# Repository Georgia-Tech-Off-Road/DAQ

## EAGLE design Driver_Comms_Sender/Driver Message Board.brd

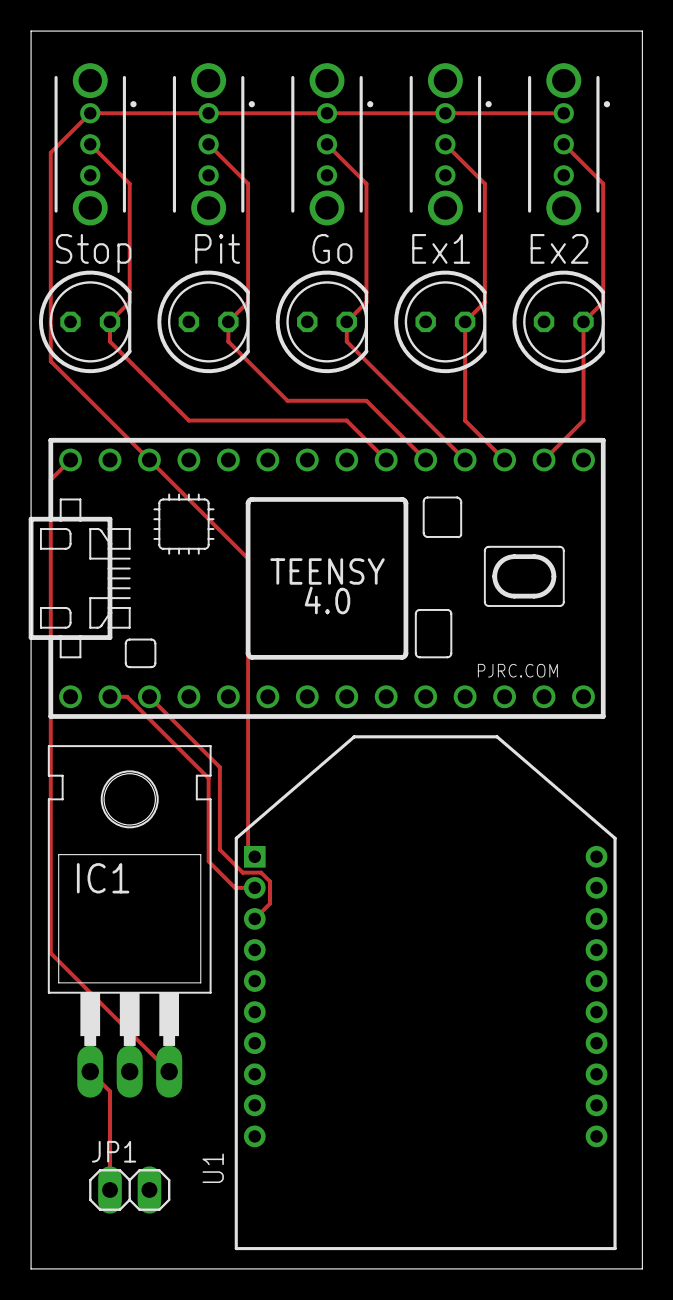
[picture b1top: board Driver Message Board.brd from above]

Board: 2 copper layers, 39.4 x 79.7 mm, 14 parts (0 on the bottom side), 11 nets.

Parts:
IC1: TO-220-H-HOLE
JP1: 1X02
LED1, LED2, LED3, LED4, LED5: LED-5MM
S1, S2, S3, S4, S5: SWITCH_SLIDE_OS102011MS2QN1; OS102011MA1QN1
U1: XBEE_PRO_S3B
U$1: TEENSY_4.0_SIMPLE

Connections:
3V_TEENSY: S1.1, S2.1, S3.1, S4.1, S5.1, U1.1, U$1.3V3_LO
+5V: IC1.3, U$1.VIN
A0: LED1.K, S1.2, U$1.14/A0
A1: LED2.K, S2.2, U$1.15/A1
A2: LED3.K, S3.2, U$1.16/A2
A3: LED4.K, S4.2, U$1.17/A3
A4: LED5.K, S5.2, U$1.18/A4/SDA
GND: IC1.2, JP1.2, LED1.A, LED2.A, LED3.A, LED4.A, LED5.A, S1.3, S2.3, S3.3, S4.3, S5.3, U1.10, U$1.GND
VCC: IC1.1, JP1.1
XBEE_RX: U1.3, U$1.1/TX
XBEE_TX: U1.2, U$1.0/RX

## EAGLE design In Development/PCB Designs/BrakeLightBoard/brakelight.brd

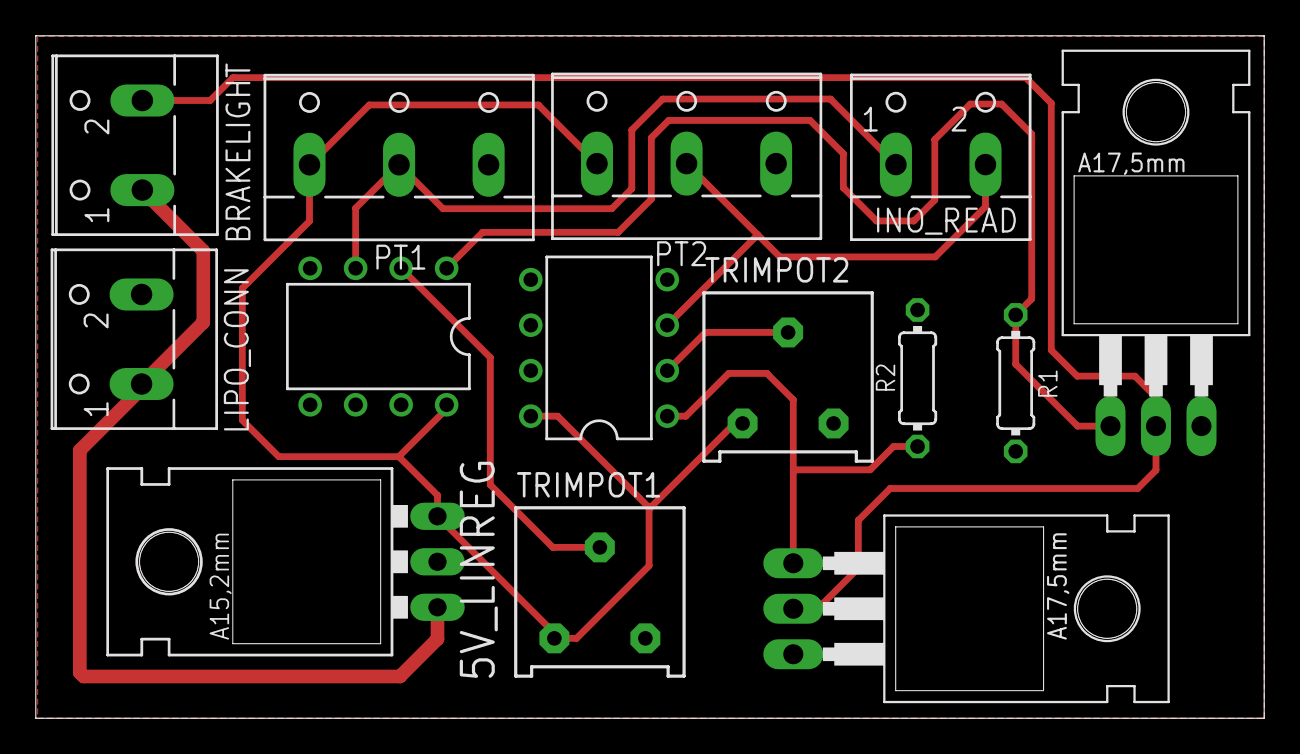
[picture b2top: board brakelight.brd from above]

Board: 2 copper layers, 68.6 x 38.1 mm, 14 parts (0 on the bottom side), 10 nets.

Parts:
5V_LINREG: 78XXL
BRAKELIGHT: W237-102
INO_READ: W237-102
LIPO_CONN: W237-102
PT1, PT2: W237-103
Q1, Q2: 75N06; TO220
R1, R2: 100k; 0204/7
TRIMPOT1, TRIMPOT2: 3386Y
U$1, U$2: LM311; DIL08

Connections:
5V: 5V_LINREG.OUT, PT1.1, PT2.1, TRIMPOT1.1, TRIMPOT2.1, U$1.8, U$2.8
GND: 5V_LINREG.GND, LIPO_CONN.2, PT1.3, PT2.3, Q1.3, Q2.3, R1.2, R2.2, TRIMPOT1.3, TRIMPOT2.3, U$1.4, U$2.4
unnamed: Q1.1, R1.1, U$1.1
unnamed: Q2.1, R2.1, U$2.1
unnamed: BRAKELIGHT.2, Q1.2, Q2.2
PT1: INO_READ.1, PT1.2, U$1.3
PT2: INO_READ.2, PT2.2, U$2.3
THRESH1: TRIMPOT1.2, U$1.2
THRESH2: TRIMPOT2.2, U$2.2
VCC: 5V_LINREG.IN, BRAKELIGHT.1, LIPO_CONN.1

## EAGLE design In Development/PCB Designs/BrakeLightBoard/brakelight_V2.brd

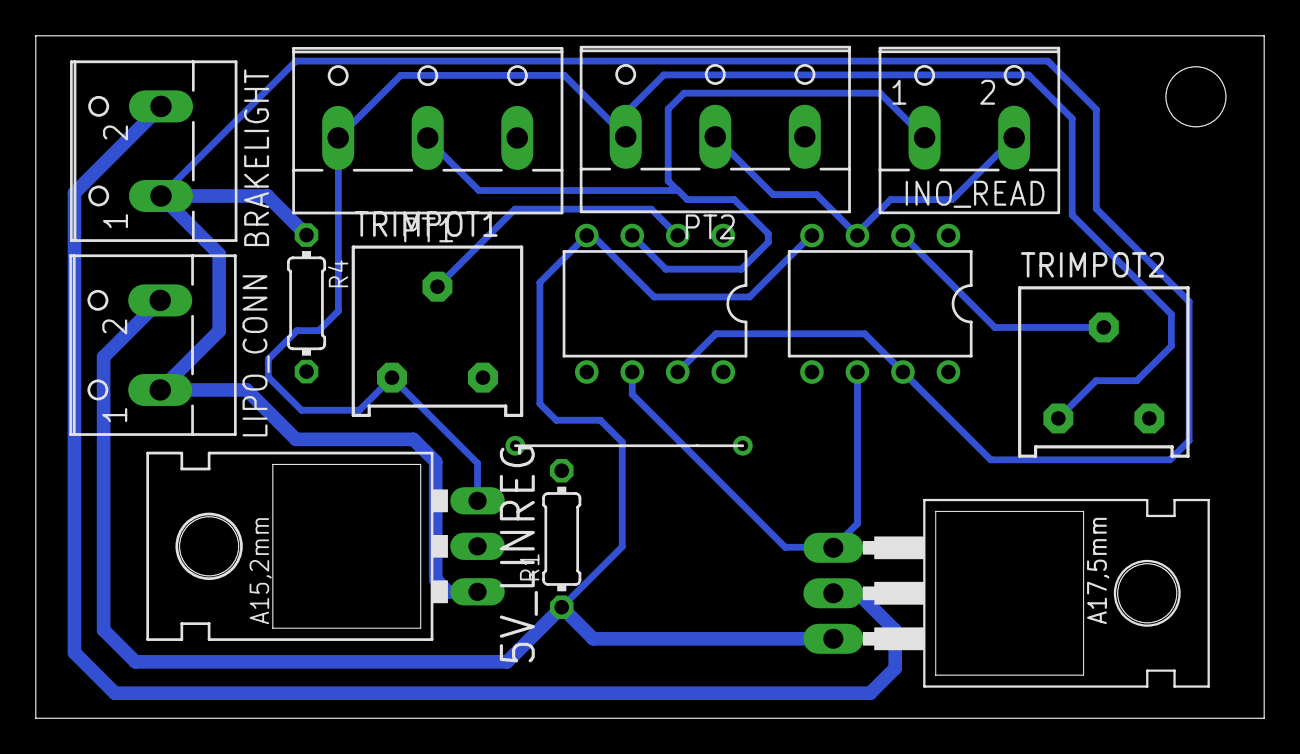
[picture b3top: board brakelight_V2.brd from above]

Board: 2 copper layers, 68.6 x 38.1 mm, 14 parts (0 on the bottom side), 10 nets.

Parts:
5V_LINREG: 78XXL
BRAKELIGHT: W237-102
INO_READ: W237-102
LIPO_CONN: W237-102
PT1, PT2: W237-103
Q2: 30N06L; TO220
R1, R4: 2.2k; 0204/7
TRIMPOT1, TRIMPOT2: 3386Y
U$1, U$2: LM741CN; DIL08
U$4: 0_OHM_RESISTOR

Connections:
0V: 5V_LINREG.GND, PT1.3, PT2.3, R1.2, R4.2, TRIMPOT1.3, TRIMPOT2.3, U$4.P$1, U$4.P$2
5V: 5V_LINREG.OUT, PT1.1, PT2.1, TRIMPOT1.1, TRIMPOT2.1
unnamed: Q2.1, U$1.6, U$2.6
unnamed: BRAKELIGHT.2, Q2.2
PT1: INO_READ.1, PT1.2, U$1.3
PT2: INO_READ.2, PT2.2, U$2.3
THRESH1: TRIMPOT1.2, U$1.2
THRESH2: TRIMPOT2.2, U$2.2
V+: 5V_LINREG.IN, BRAKELIGHT.1, LIPO_CONN.1, R4.1, U$1.7, U$2.7
V-: LIPO_CONN.2, Q2.3, R1.1, U$1.4, U$2.4

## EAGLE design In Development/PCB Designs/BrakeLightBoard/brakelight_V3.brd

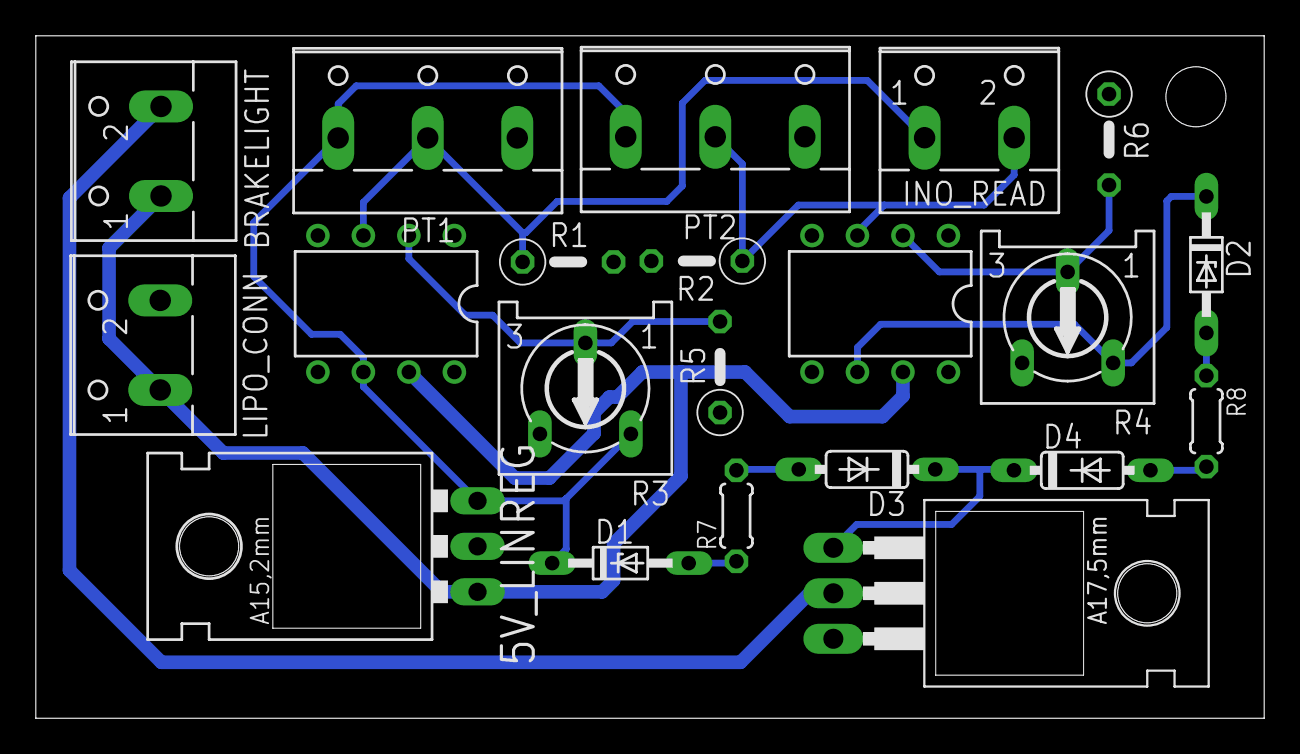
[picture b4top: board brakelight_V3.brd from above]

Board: 2 copper layers, 68.6 x 38.1 mm, 21 parts (0 on the bottom side), 14 nets.

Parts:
5V_LINREG: 78XXL
BRAKELIGHT: W237-102
D1, D2: 1N5231; DO34Z7
D3, D4: 1N4148DO35-7; DO35-7
INO_READ: W237-102
LIPO_CONN: W237-102
PT1, PT2: W237-103
Q2: 30N06L; TO220
R1, R2: 5.1k; 0207/5V
R3, R4: 10k; RS3
R5, R6: 560; 0207/5V
R7, R8: 1k; 0204/5
U$1, U$2: LM741; DIL08

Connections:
5V: 5V_LINREG.OUT, D1.C, PT1.1, PT2.1, R3.A, U$1.6
GND: 5V_LINREG.GND, LIPO_CONN.2, PT1.3, PT2.3, Q2.3, R1.2, R2.2, R5.1, R6.1, U$1.1, U$1.4, U$1.5, U$2.1, U$2.4, U$2.5
unnamed: D2.C, R4.A, U$2.6
unnamed: BRAKELIGHT.2, Q2.2
unnamed: D3.A, R7.2
unnamed: D4.A, R8.2
unnamed: D1.A, R7.1
unnamed: D2.A, R8.1
unnamed: D3.C, D4.C, Q2.1
PT1: INO_READ.1, PT1.2, R1.1, U$1.3
PT2: INO_READ.2, PT2.2, R2.1, U$2.3
THRESH1: R3.S, R5.2, U$1.2
THRESH2: R4.S, R6.2, U$2.2
VCC: 5V_LINREG.IN, BRAKELIGHT.1, LIPO_CONN.1, U$1.7, U$2.7

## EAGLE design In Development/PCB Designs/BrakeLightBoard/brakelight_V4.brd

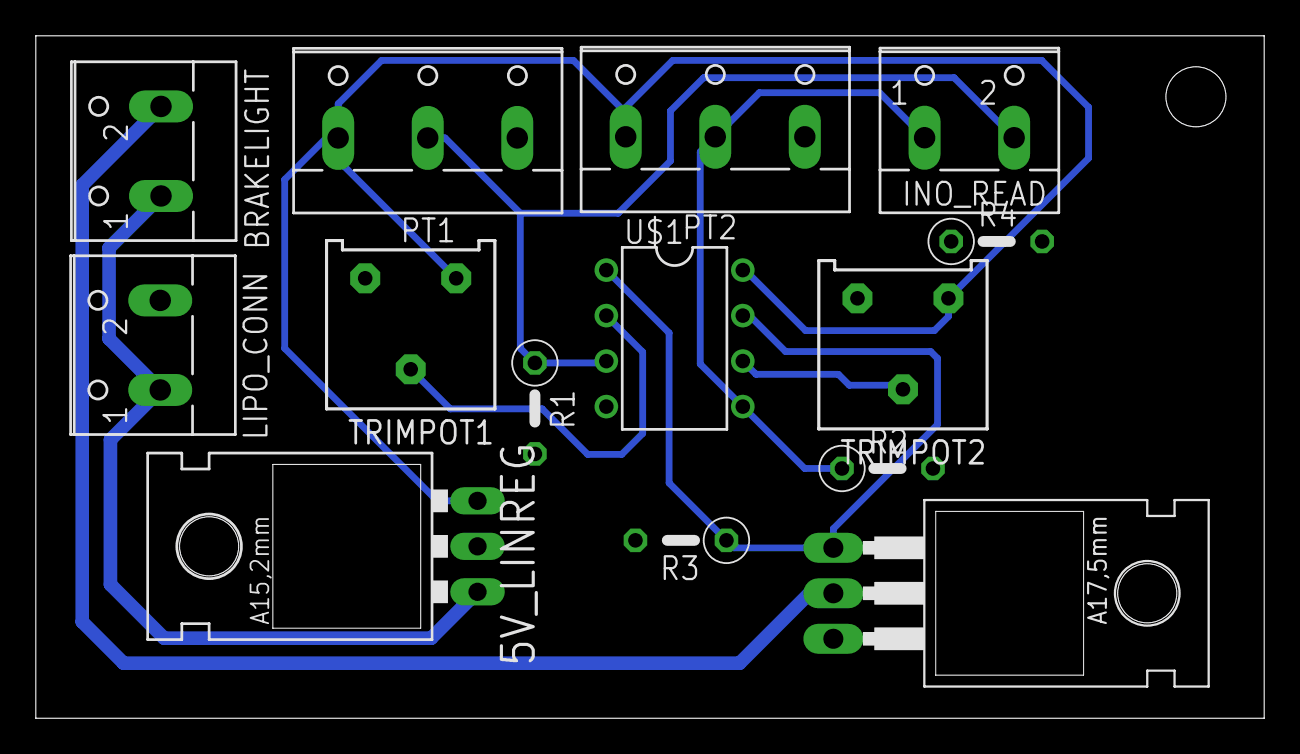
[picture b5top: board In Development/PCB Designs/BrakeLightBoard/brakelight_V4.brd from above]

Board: 2 copper layers, 68.6 x 38.1 mm, 14 parts (0 on the bottom side), 9 nets.

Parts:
5V_LINREG: 78XXL
BRAKELIGHT: W237-102
INO_READ: W237-102
LIPO_CONN: W237-102
PT1, PT2: W237-103
Q2: 30N06L; TO220
R1, R2, R3, R4: 0207/5V
TRIMPOT1, TRIMPOT2: 3386Y
U$1: TLC2252; DIL08

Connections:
5V: 5V_LINREG.OUT, PT1.1, PT2.1, TRIMPOT1.1, TRIMPOT2.1, U$1.8
GND: 5V_LINREG.GND, LIPO_CONN.2, PT1.3, PT2.3, Q2.3, R1.2, R2.2, R4.1, R4.2, TRIMPOT1.3, TRIMPOT2.3, U$1.4
unnamed: BRAKELIGHT.2, Q2.2
unnamed: Q2.1, R3.1, U$1.1, U$1.7
PT1: INO_READ.2, PT1.2, R1.1, U$1.3
PT2: INO_READ.1, PT2.2, R2.1, U$1.5
VCC: 5V_LINREG.IN, BRAKELIGHT.1, LIPO_CONN.1
VREF1: TRIMPOT1.2, U$1.2
VREF2: TRIMPOT2.2, U$1.6

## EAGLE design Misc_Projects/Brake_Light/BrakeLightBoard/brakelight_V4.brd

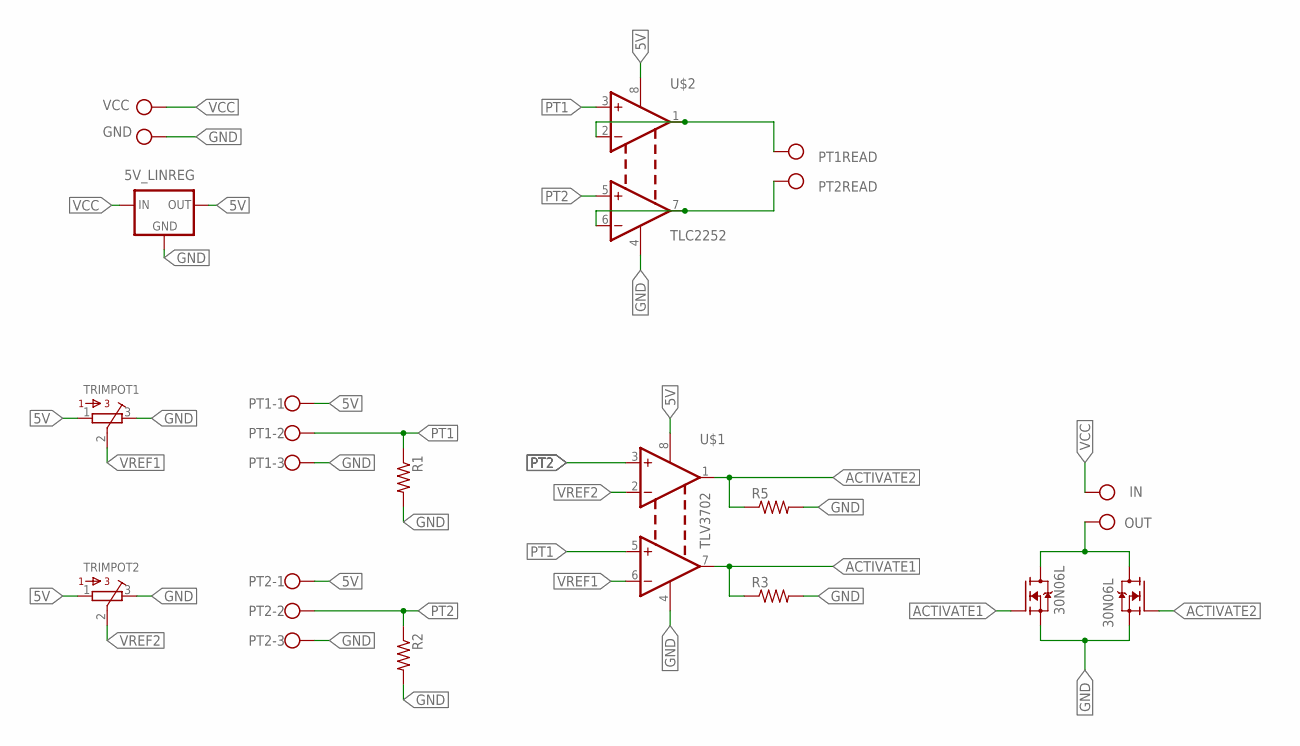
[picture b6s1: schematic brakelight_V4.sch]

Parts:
5V_LINREG: 78XXS
BRAKELIGHT: W237-102
INO_READ: W237-102
LIPO_CONN: W237-102
PT1, PT2: W237-103
Q1, Q2: 30N06L; TO220V
R1, R2, R3, R5: R-US_0207/5V; 0207/5V
TRIMPOT1, TRIMPOT2: 3386-Y; 3386Y
U$1: TLV3702; DIL08
U$2: TLC2252; DIL08

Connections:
5V: 5V_LINREG.OUT, PT1.1, PT2.1, TRIMPOT1.1, TRIMPOT2.1, U$1.8 (V+), U$2.8 (V+)
ACTIVATE1: Q2.1 (G), R3.1, U$1.7 (2OUT)
ACTIVATE2: Q1.1 (G), R5.1, U$1.1 (1OUT)
GND: 5V_LINREG.GND, LIPO_CONN.2, PT1.3, PT2.3, Q1.3 (S), Q2.3 (S), R1.2, R2.2, R3.2, R5.2, TRIMPOT1.3, TRIMPOT2.3, U$1.4 (V-), U$2.4 (V-)
unnamed: BRAKELIGHT.2, Q1.2 (D), Q2.2 (D)
unnamed: INO_READ.1, U$2.1 (1OUT), U$2.2 (1IN-)
unnamed: INO_READ.2, U$2.6 (2IN-), U$2.7 (2OUT)
PT1: PT1.2, R1.1, U$1.5 (2IN+), U$2.3 (1IN+)
PT2: PT2.2, R2.1, U$1.3 (1IN+), U$2.5 (2IN+)
VCC: 5V_LINREG.IN, BRAKELIGHT.1, LIPO_CONN.1
VREF1: TRIMPOT1.2, U$1.6 (2IN-)
VREF2: TRIMPOT2.2, U$1.2 (1IN-)

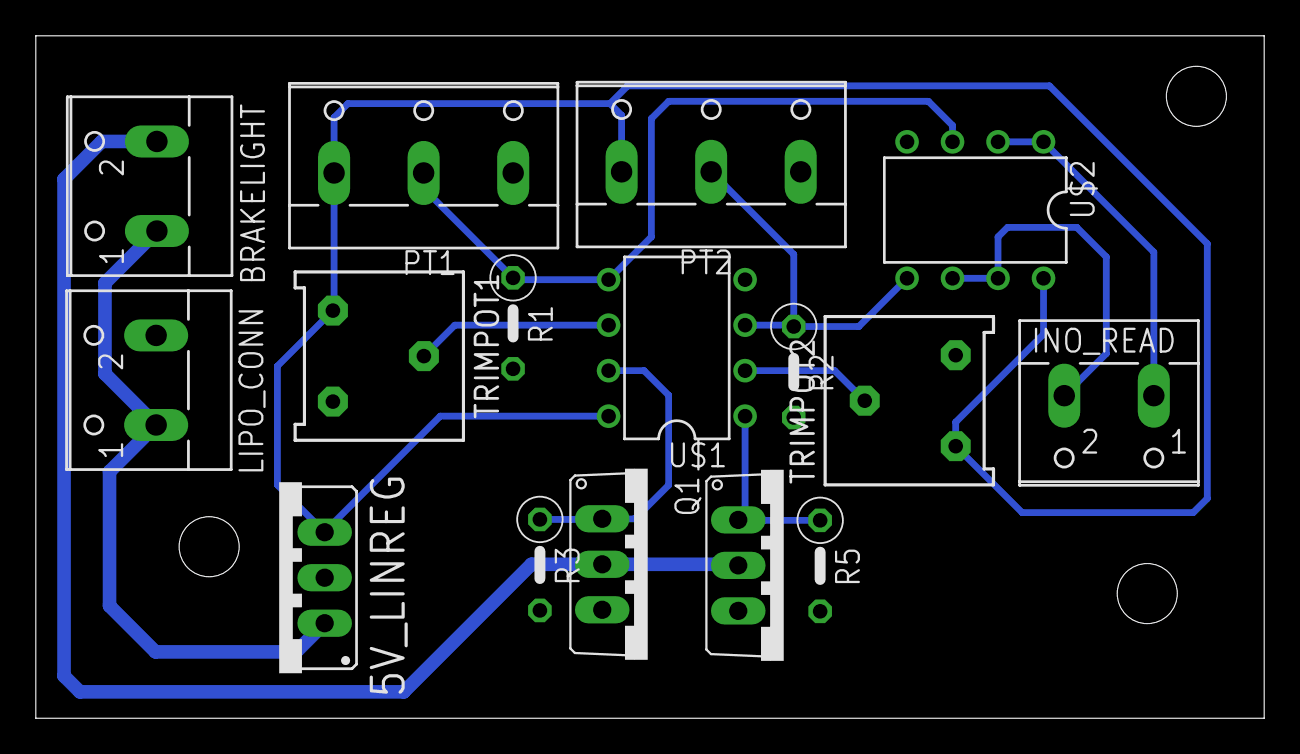
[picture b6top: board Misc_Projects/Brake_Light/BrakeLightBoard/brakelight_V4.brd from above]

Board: 2 copper layers, 68.6 x 38.1 mm, 19 parts (0 on the bottom side), 12 nets.

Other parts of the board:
U$3, U$4, U$5: SOLE_HOLE

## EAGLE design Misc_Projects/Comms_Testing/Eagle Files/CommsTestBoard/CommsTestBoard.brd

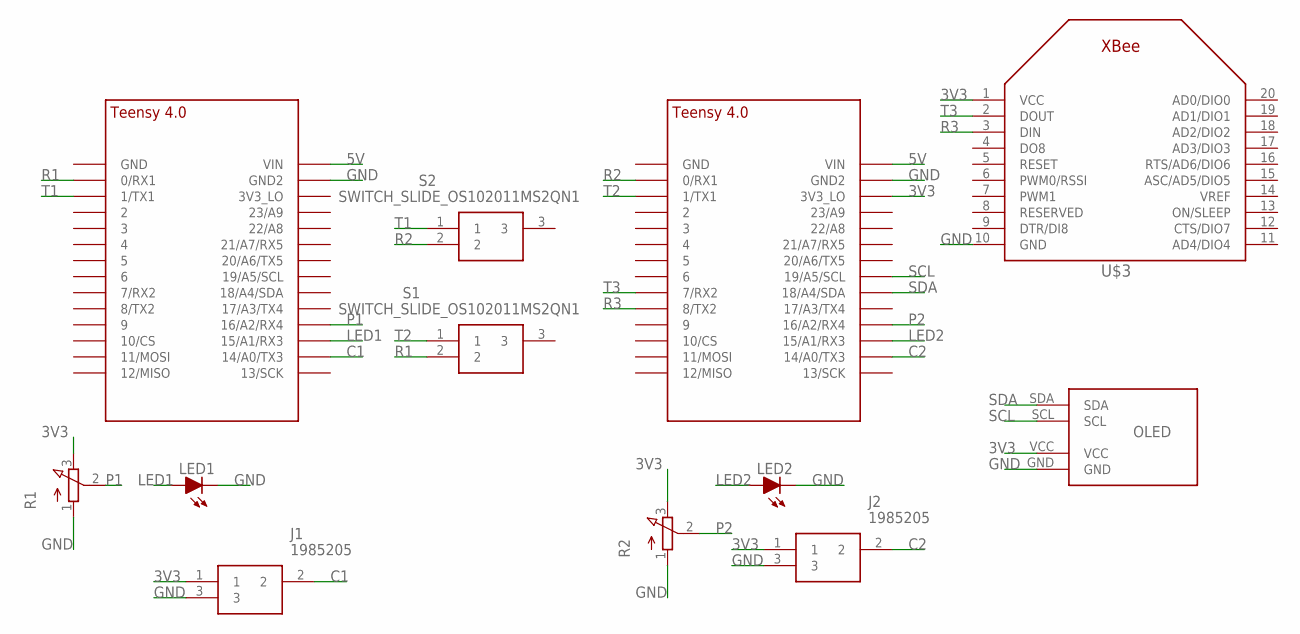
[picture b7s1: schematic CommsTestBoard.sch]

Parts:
J1, J2: 1985205
LED1, LED2: LED-5MM
R1, R2: POTENTIOMETER; 3RP/1610N
S1, S2: SWITCH_SLIDE_OS102011MS2QN1; OS102011MA1QN1
U$1, U$2: TEENSY_4.0_SIMPLE
U$3: XBEE
U$4: OLED_SSD1306

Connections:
3V3: J1.1, J2.1, R1.3 (E), R2.3 (E), U$2.3V3_LO, U$3.1 (VCC), U$4.VCC
5V: U$1.VIN, U$2.VIN
C1: J1.2, U$1.14/A0 (14/A0/TX3)
C2: J2.2, U$2.14/A0 (14/A0/TX3)
GND: J1.3, J2.3, LED1.K (C), LED2.K (C), R1.1 (A), R2.1 (A), U$1.GND2, U$2.GND2, U$3.10 (GND), U$4.GND
LED1: LED1.A, U$1.15/A1 (15/A1/RX3)
LED2: LED2.A, U$2.15/A1 (15/A1/RX3)
P1: R1.2 (S), U$1.16/A2 (16/A2/RX4)
P2: R2.2 (S), U$2.16/A2 (16/A2/RX4)
R1: S1.2, U$1.0/RX (0/RX1)
R2: S2.2, U$2.0/RX (0/RX1)
R3: U$2.8 (8/TX2), U$3.3 (DIN)
SCL: U$2.19/A5/SCL, U$4.SCL
SDA: U$2.18/A4/SDA, U$4.SDA
T1: S2.1, U$1.1/TX (1/TX1)
T2: S1.1, U$2.1/TX (1/TX1)
T3: U$2.7 (7/RX2), U$3.2 (DOUT)

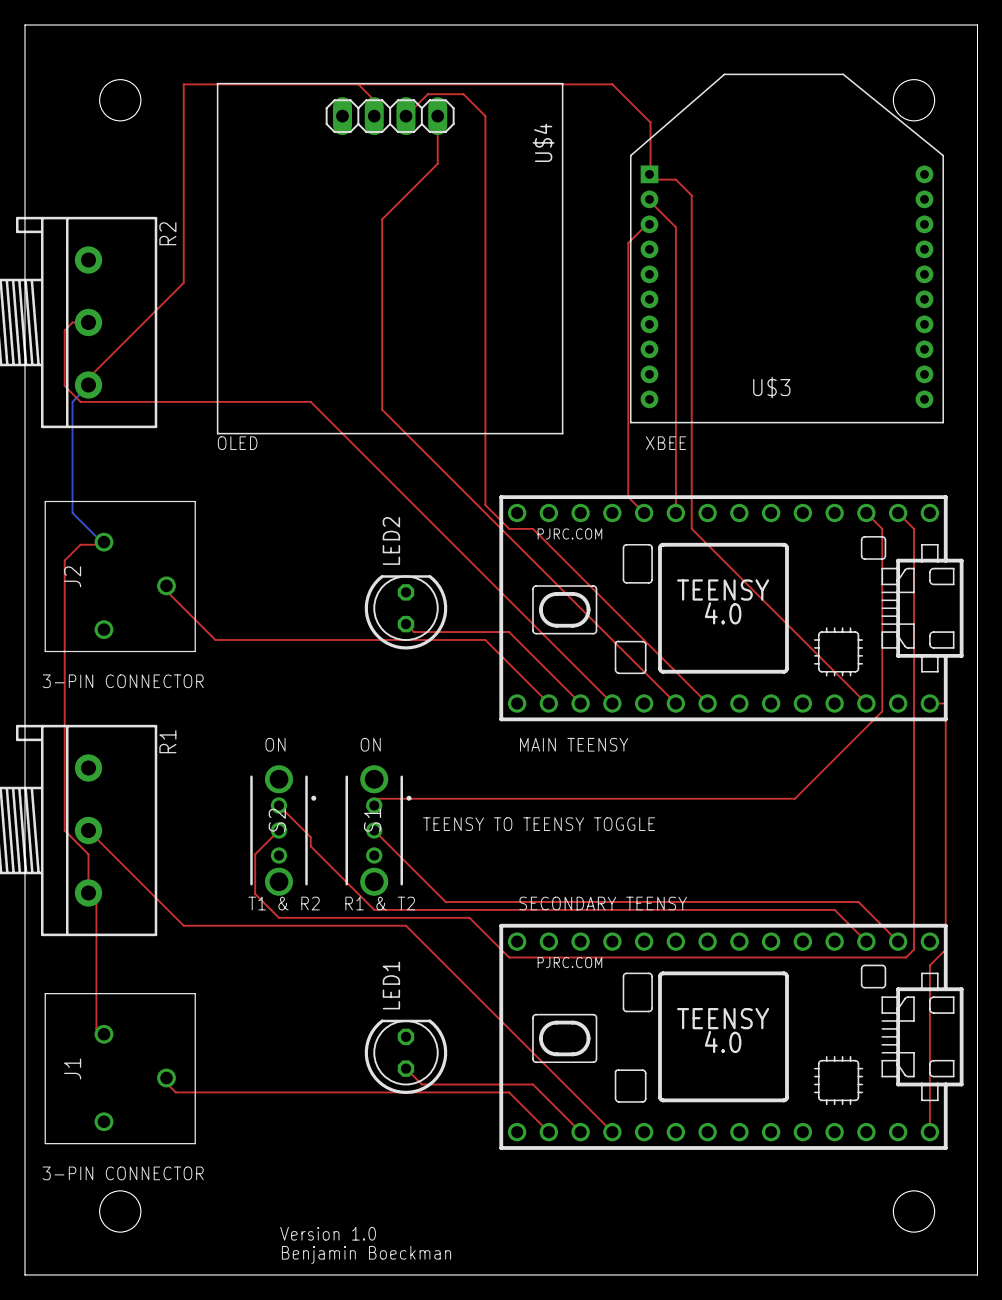
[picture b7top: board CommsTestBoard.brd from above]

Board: 2 copper layers, 76.2 x 100.0 mm, 12 parts (0 on the bottom side), 17 nets.

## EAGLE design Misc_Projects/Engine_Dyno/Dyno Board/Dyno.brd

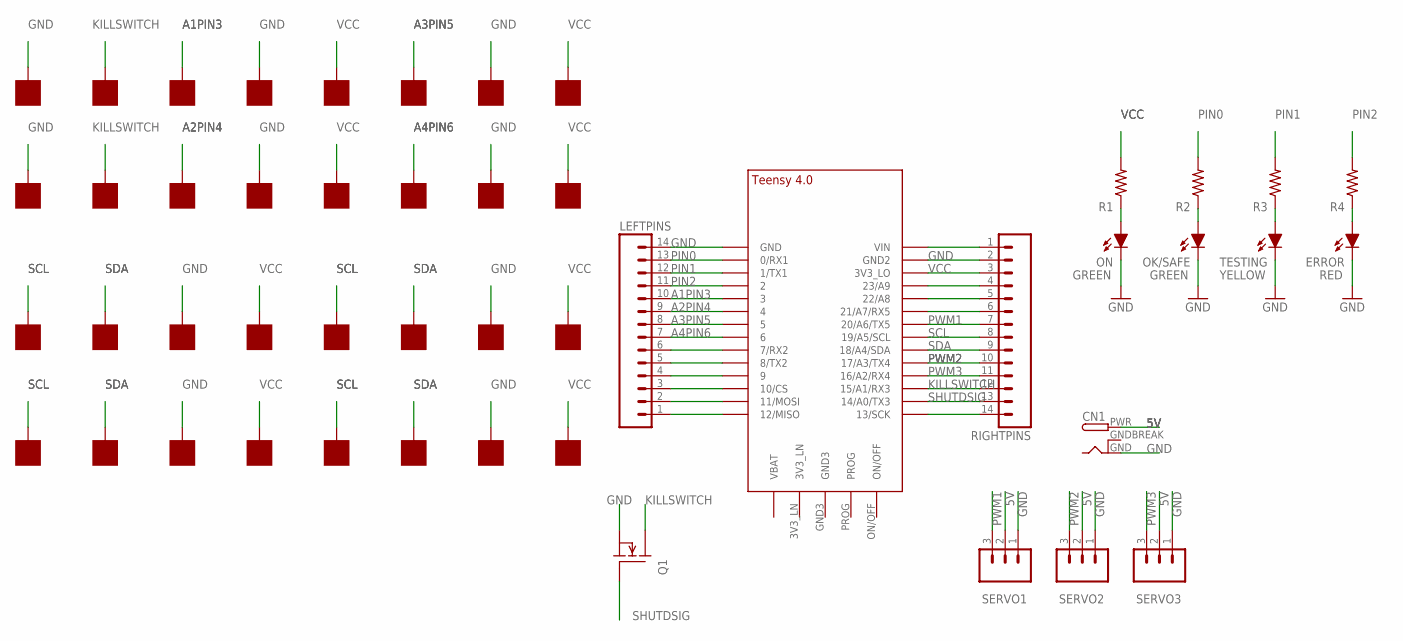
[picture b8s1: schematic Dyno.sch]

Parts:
A1, A1GND, A1VCC, A2, A2GND, A2VCC, A3, A3GND, A3VCC, A4, A4GND, A4VCC: SOLDER_PAD; SOLDER_PAD_XSMALL
CN1: DCBARRELPTH; DCJACK_2MM_PTH
EMERGENCYSTOPBUTTON: SOLDER_PAD; SOLDER_PAD_XSMALL
ERROR: RED; LED-5MM
GNDBUTTON: SOLDER_PAD; SOLDER_PAD_XSMALL
GNDKILL: SOLDER_PAD; SOLDER_PAD_XSMALL
I2CGND1, I2CGND2, I2CGND3, I2CGND4, I2CVCC1, I2CVCC2, I2CVCC3, I2CVCC4: SOLDER_PAD; SOLDER_PAD_XSMALL
KILLSWITCH: SOLDER_PAD; SOLDER_PAD_XSMALL
LEFTPINS: M14; 14P
OK/SAFE: GREEN; LED-5MM
ON: GREEN; LED-5MM
Q1: DMG3406LSOT; SOT23
R1, R2, R3, R4: RESISTOR0603-RES; 0603-RES
RIGHTPINS: M14; 14P
SCL1, SCL2, SCL3, SCL4: SOLDER_PAD; SOLDER_PAD_XSMALL
SDA1, SDA2, SDA3, SDA4: SOLDER_PAD; SOLDER_PAD_XSMALL
SERVO1, SERVO2, SERVO3: M03; 1X03
TESTING: YELLOW; LED-5MM
U$1: TEENSY_4.0

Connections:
5V: CN1.PWR, SERVO1.2, SERVO2.2, SERVO3.2
A1PIN3: A1.P$1, LEFTPINS.10, U$1.3/CANTX (3)
A2PIN4: A2.P$1, LEFTPINS.9, U$1.4/CANRX (4)
A3PIN5: A3.P$1, LEFTPINS.8, U$1.5
A4PIN6: A4.P$1, LEFTPINS.7, U$1.6
GND: A1GND.P$1, A2GND.P$1, A3GND.P$1, A4GND.P$1, CN1.GND, ERROR.K (C), GNDBUTTON.P$1, GNDKILL.P$1, I2CGND1.P$1, I2CGND2.P$1, I2CGND3.P$1, I2CGND4.P$1, LEFTPINS.14, OK/SAFE.K (C), ON.K (C), Q1.2 (S), RIGHTPINS.2, SERVO1.1, SERVO2.1, SERVO3.1, TESTING.K (C), U$1.GND, U$1.GND2
GNDBREAK: CN1.GNDBREAK
KILLSWITCH: EMERGENCYSTOPBUTTON.P$1, KILLSWITCH.P$1, Q1.3 (D), RIGHTPINS.12, U$1.15/A1 (15/A1/RX3)
unnamed: LEFTPINS.6, U$1.7 (7/RX2)
unnamed: LEFTPINS.5, U$1.8 (8/TX2)
unnamed: LEFTPINS.4, U$1.9/CS (9)
unnamed: LEFTPINS.3, U$1.10/CS
unnamed: LEFTPINS.2, U$1.11/MOSI
unnamed: LEFTPINS.1, U$1.12/MISO
unnamed: RIGHTPINS.1, U$1.VIN
unnamed: RIGHTPINS.4, U$1.23/A9
unnamed: RIGHTPINS.5, U$1.22/A8
unnamed: RIGHTPINS.6, U$1.21/A7 (21/A7/RX5)
unnamed: RIGHTPINS.14, U$1.13/SCK
unnamed: ON.A, R1.1
unnamed: OK/SAFE.A, R2.1
unnamed: R3.1, TESTING.A
unnamed: ERROR.A, R4.1
PIN0: LEFTPINS.13, R2.2, U$1.0/RX (0/RX1)
PIN1: LEFTPINS.12, R3.2, U$1.1/TX (1/TX1)
PIN2: LEFTPINS.11, R4.2, U$1.2
PWM1: RIGHTPINS.7, SERVO1.3, U$1.20/A6 (20/A6/TX5)
PWM2: RIGHTPINS.10, SERVO2.3, U$1.17/A3 (17/A3/TX4)
PWM3: RIGHTPINS.11, SERVO3.3, U$1.16/A2 (16/A2/RX4)
SCL: RIGHTPINS.8, SCL1.P$1, SCL2.P$1, SCL3.P$1, SCL4.P$1, U$1.19/A5/SCL
SDA: RIGHTPINS.9, SDA1.P$1, SDA2.P$1, SDA3.P$1, SDA4.P$1, U$1.18/A4/SDA
SHUTDSIG: Q1.1 (G), RIGHTPINS.13, U$1.14/A0 (14/A0/TX3)
VCC: A1VCC.P$1, A2VCC.P$1, A3VCC.P$1, A4VCC.P$1, I2CVCC1.P$1, I2CVCC2.P$1, I2CVCC3.P$1, I2CVCC4.P$1, R1.2, RIGHTPINS.3, U$1.3V3_LO

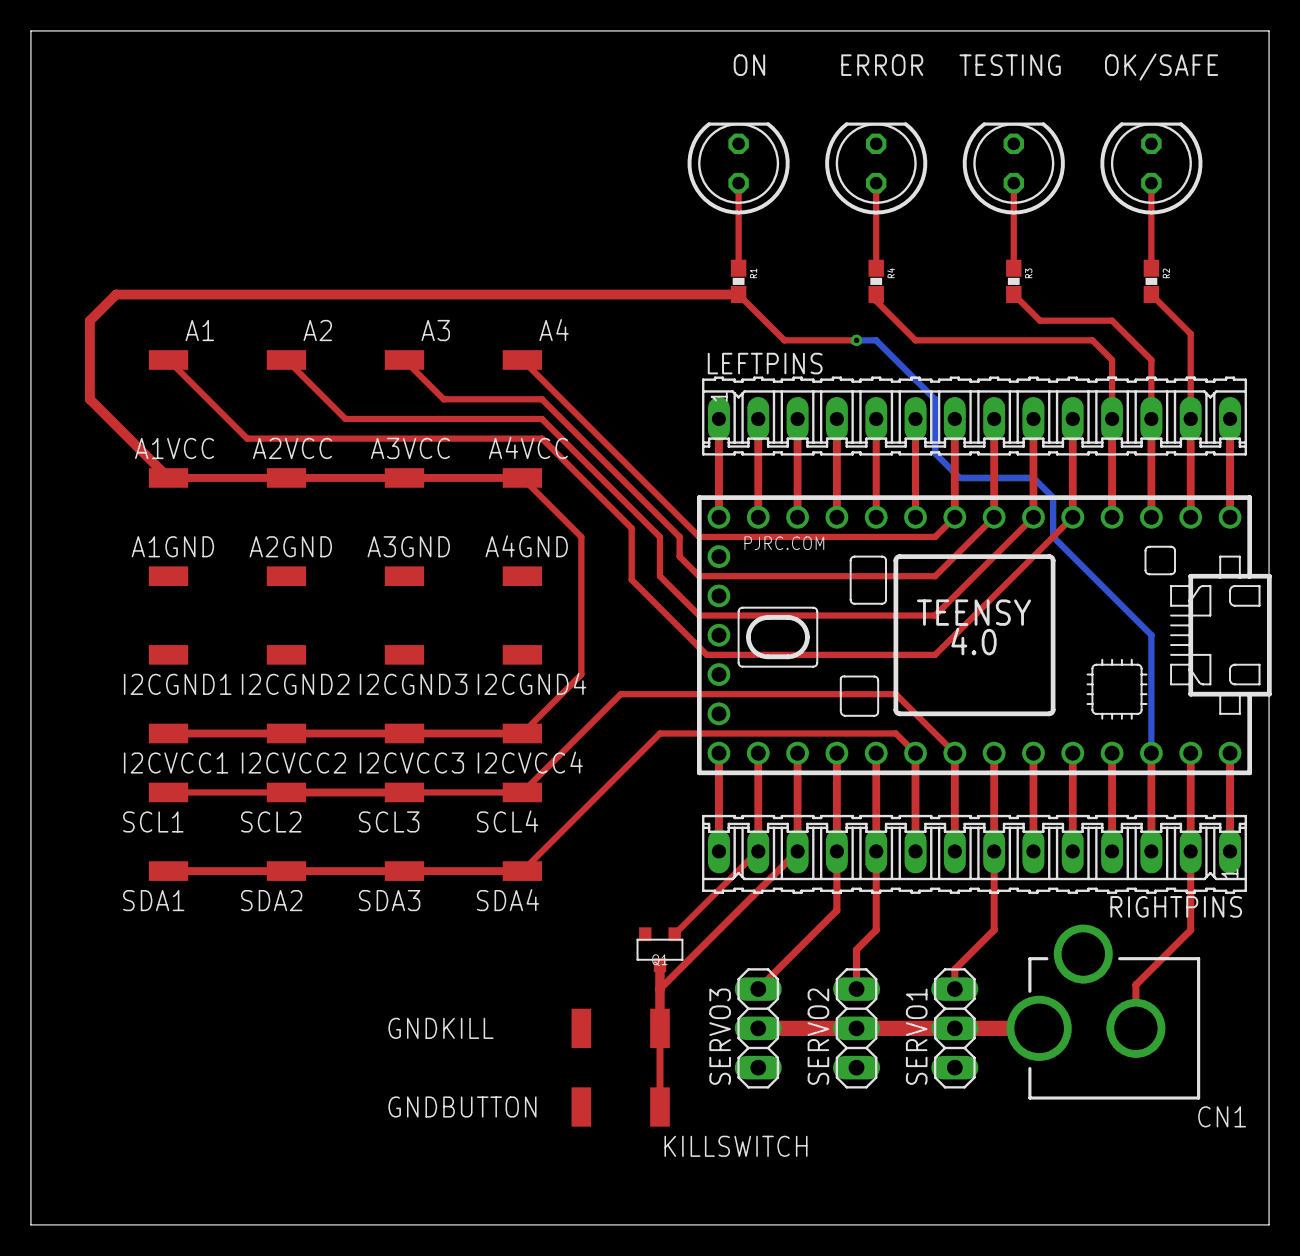
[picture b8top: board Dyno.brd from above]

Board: 2 copper layers, 80.0 x 77.1 mm, 48 parts (0 on the bottom side), 32 nets.
